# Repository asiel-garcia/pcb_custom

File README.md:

# pcb_custom
Custom PCB made on KiCad

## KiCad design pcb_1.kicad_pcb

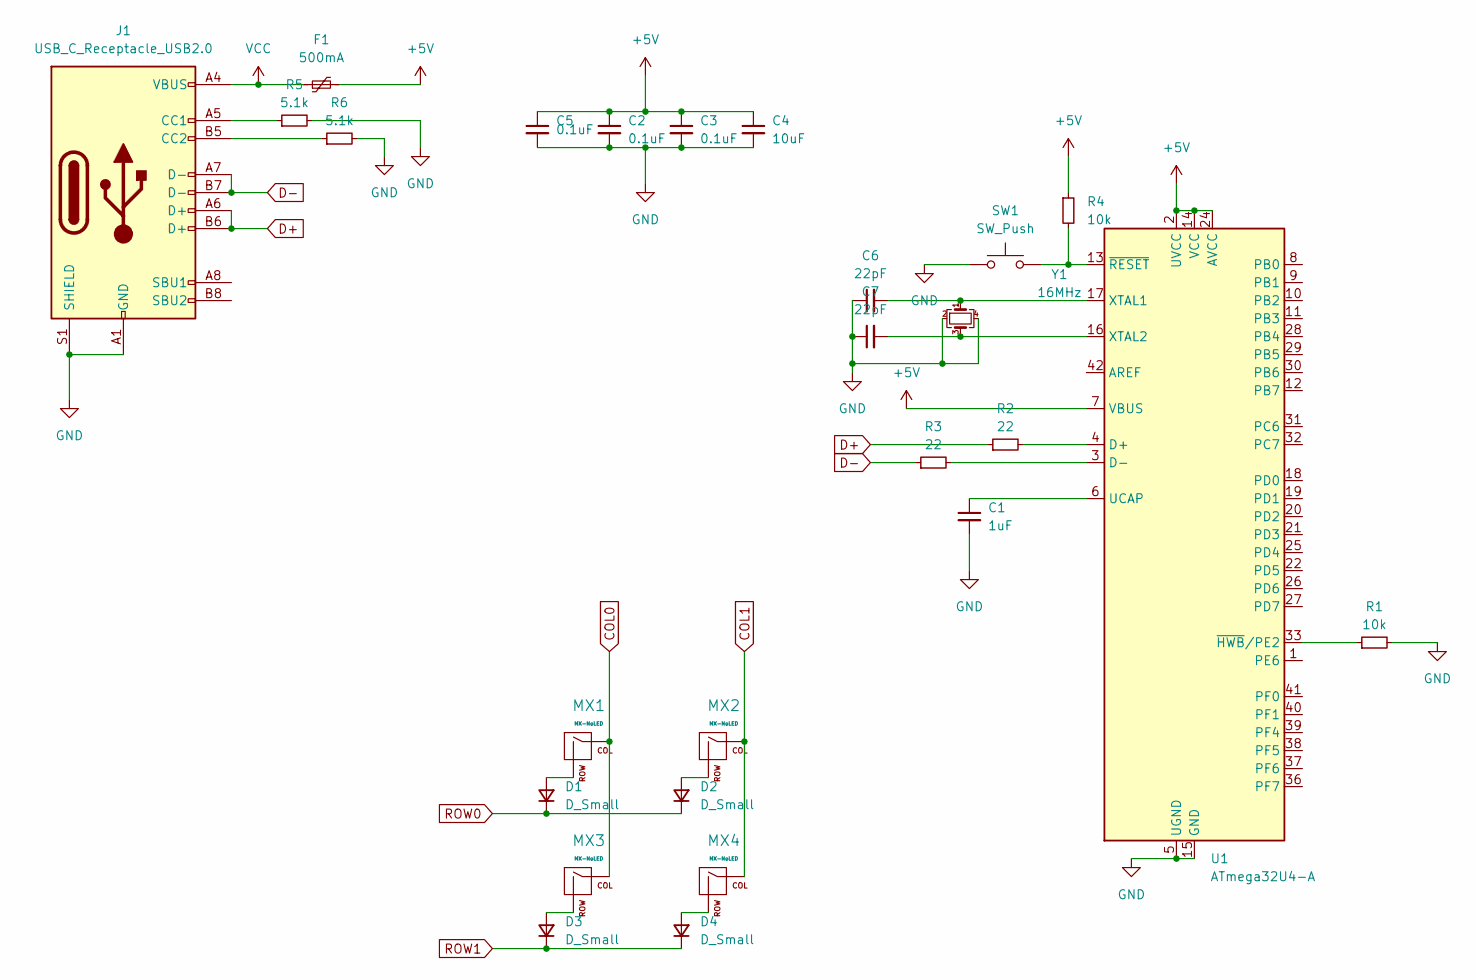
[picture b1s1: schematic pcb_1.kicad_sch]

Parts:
C1: 1uF; C_0805_2012Metric
C2, C3, C5: 0.1uF; C_0805_2012Metric
C4: 10uF; C_0805_2012Metric
C6, C7: 22pF; C_0805_2012Metric
D1, D2, D3, D4: D_Small; D_SOD-123
F1: 500mA; Fuse_1206_3216Metric
J1: USB_C_Receptacle_USB2.0; USB_C_Receptacle_HCTL_HC-TYPE-C-16P-01A
MX1, MX2, MX3, MX4: MX-NoLED; MX-1U-NoLED
R1, R4: 10k; R_0805_2012Metric
R2, R3: 22; R_0805_2012Metric
R5, R6: 5.1k; R_0805_2012Metric
SW1: SW_Push; SKQG-1155865
U1: ATmega32U4-A; TQFP-44_10x10mm_P0.8mm
Y1: 16MHz; Crystal_SMD_3225-4Pin_3.2x2.5mm

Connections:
+5V: C2.1, C3.1, C4.1, C5.1, F1.2, R4.1, U1.2 (UVCC), U1.7 (VBUS), U1.14 (VCC), U1.24 (AVCC), U1.34 (VCC), U1.44 (AVCC)
COL0: MX1.1 (COL), MX3.1 (COL)
COL1: MX2.1 (COL), MX4.1 (COL)
D+: J1.A6 (D+), J1.B6 (D+), R2.1
D-: J1.A7 (D-), J1.B7 (D-), R3.1
GND: C1.2, C2.2, C3.2, C4.2, C5.2, C6.1, C7.1, J1.A1 (GND), J1.A12 (GND), J1.B1 (GND), J1.B12 (GND), J1.S1 (SHIELD), R1.2, R5.2, R6.2, SW1.1, U1.5 (UGND), U1.15 (GND), U1.23 (GND), U1.35 (GND), U1.43 (GND), Y1.2, Y1.4
unnamed: D1.2 (A), MX1.2 (ROW)
unnamed: D2.2 (A), MX2.2 (ROW)
unnamed: D3.2 (A), MX3.2 (ROW)
unnamed: D4.2 (A), MX4.2 (ROW)
unnamed: J1.A5 (CC1), R5.1
unnamed: J1.B5 (CC2), R6.1
unnamed: R2.2, U1.4 (D+)
unnamed: R3.2, U1.3 (D-)
unnamed: C1.1, U1.6 (UCAP)
unnamed: C6.2, U1.17 (XTAL1), Y1.1
unnamed: C7.2, U1.16 (XTAL2), Y1.3
unnamed: R1.1, U1.33 (~HWB/PE2)
unnamed: R4.2, SW1.2, U1.13 (~RESET)
ROW0: D1.1 (K), D2.1 (K)
ROW1: D3.1 (K), D4.1 (K)
VCC: F1.1, J1.A4 (VBUS), J1.A9 (VBUS), J1.B4 (VBUS), J1.B9 (VBUS)

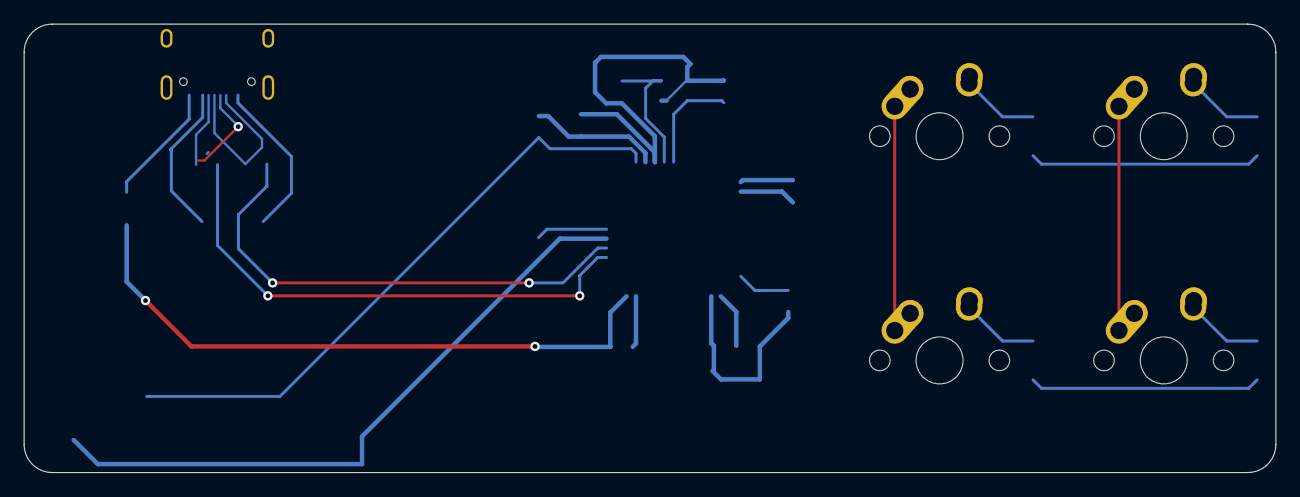
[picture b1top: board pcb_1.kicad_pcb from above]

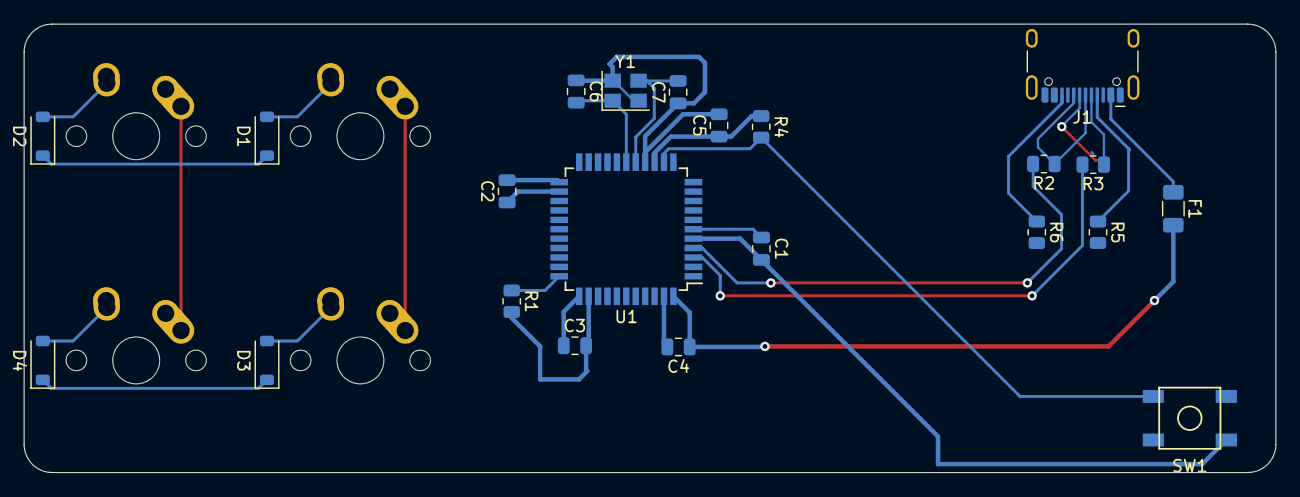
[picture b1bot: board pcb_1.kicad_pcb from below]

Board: 2 copper layers, 106.4 x 38.1 mm, 26 parts (22 on the bottom side), 22 nets.

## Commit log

2023-11-02 Add submodules
2023-11-02 Project specific libraries
2023-11-02 Schematic
2023-11-02 pcb layout - 1
